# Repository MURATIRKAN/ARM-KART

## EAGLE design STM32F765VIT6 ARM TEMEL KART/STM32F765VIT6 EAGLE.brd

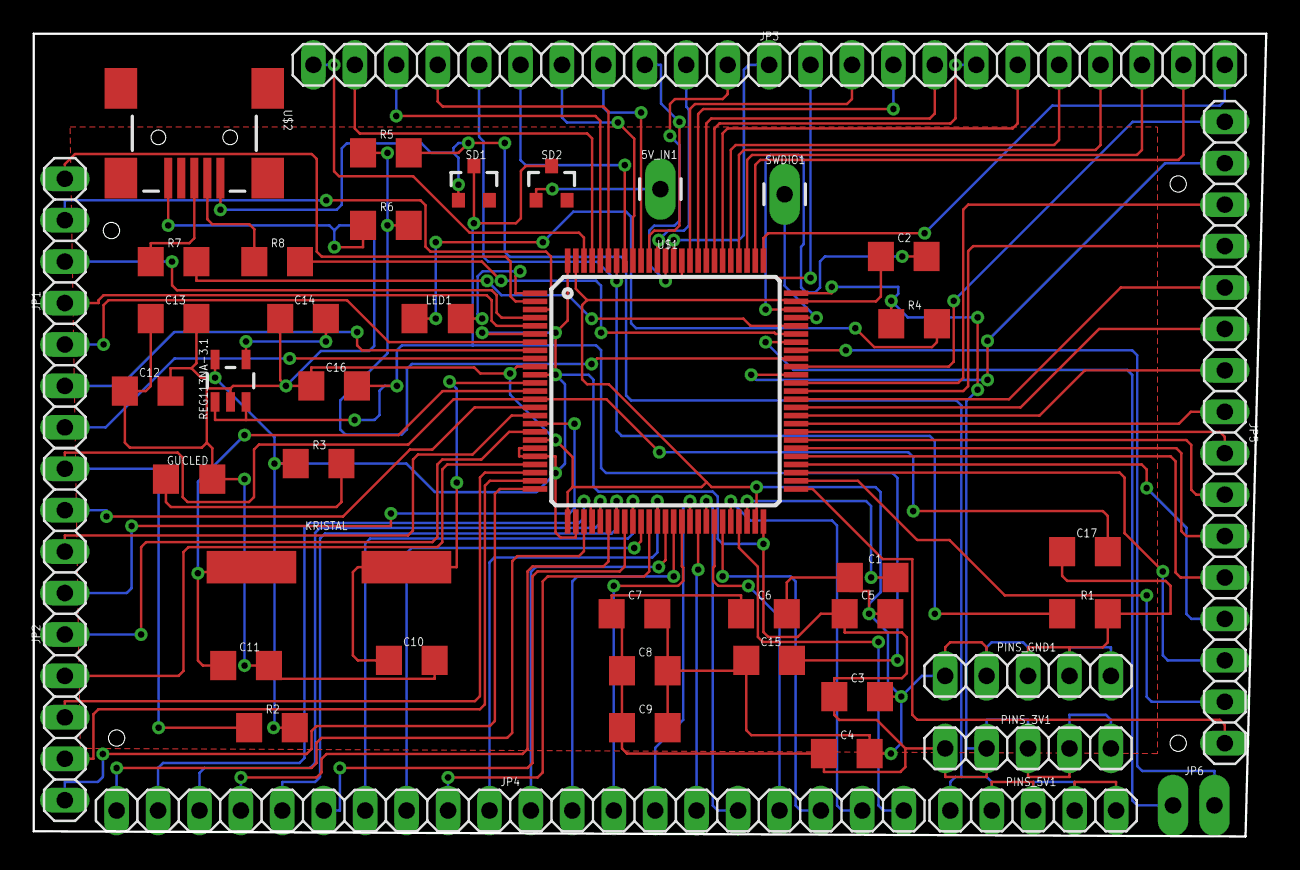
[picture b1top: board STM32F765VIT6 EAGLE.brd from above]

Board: 2 copper layers, 75.6 x 49.2 mm, 44 parts (0 on the bottom side), 95 nets.

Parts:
5V_IN1: M01PTH_LONGPAD (M01); 1X01_LONGPAD
C1, C2, C9: 2uF2; 1206
C3, C4, C5, C6, C7, C17: 100nF; 1206
C8, C12, C13, C14, C15, C16: 10nF; 1206
C10, C11: 18pF; 1206
GUCLED: GREEN; 1206_GUCLED
JP1: PINHD-1X07_2.54 (PINHD-1X07); 1X07
JP2: PINHD-1X09_2.54 (PINHD-1X09); 1X09
JP3: PINHD-1X23_2.54 (PINHD-1X23); 1X23
JP4: PINHD-1X20_2.54 (PINHD-1X20); 1X20
JP5: PINHD-1X16_2.54 (PINHD-1X16); 1X16
JP6: M02; 1X02_LONGPADS
KRISTAL: 8MHZ; CSM-7X-DU
LED1: BLUE; 1206_GUCLED
PINS_3V1, PINS_5V1: PINHD-1X05_2.54 (PINHD-1X05); 1X05
PINS_GND1: PINHD-1X05_2.54 (PINHD-1X05); 1X05
R1, R2: 10K; 1206
R3, R4: 330; 1206
R5: 15K; 1206
R6: 22K; 1206
R7, R8: 22; 1206
REG113NA-3.1: V_REG_LDOSMD (V_REG_LDO); SOT23-5
SD1, SD2: 400mA/40V/470mV; SOT23-3
SWDIO1: M01PTH_LONGPAD (M01); 1X01_LONGPAD
U$1: STM32F765VIT6; LQFP100
U$2: USB-MINIB-5PIN (USB-MINIB); USB-MINIB

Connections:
2_PE3: JP1.7, U$1.2
3V3: C3.1, C4.1, C5.1, C6.1, C7.1, C8.1, C9.1, C12.2, C13.2, PINS_3V1.1, PINS_3V1.2, PINS_3V1.3, PINS_3V1.4, PINS_3V1.5, R2.2, R3.1, R4.1, REG113NA-3.1.5, U$1.6, U$1.11, U$1.20, U$1.21, U$1.27, U$1.50, U$1.75, U$1.100
3_PE4: JP1.6, U$1.3
4_PE5: JP1.5, U$1.4
5V: 5V_IN1.1, SD2.1
5_PE6: JP1.4, U$1.5
7_PC13: JP1.3, U$1.7
8_PC14: JP1.2, U$1.8
9_PC15: JP1.1, U$1.9
15_PC0: JP2.8, U$1.15
16_PC1: JP2.7, U$1.16
17_PC2: JP2.6, U$1.17
18_PC3: JP2.5, U$1.18
22_PA0: JP2.4, U$1.22
23_PA1: JP2.3, U$1.23
24_PA2: JP2.2, U$1.24
25_PA3: JP2.1, U$1.25
28_PA4: JP4.1, U$1.28
29_PA5: JP4.2, U$1.29
30_PA6: JP4.3, U$1.30
31_PA7: JP4.4, U$1.31
32_PC4: JP4.5, U$1.32
33_PC5: JP4.6, U$1.33
34_PB0: JP4.7, U$1.34
35_PB1: JP4.8, U$1.35
36_PB2: JP4.9, U$1.36
37_PE7: JP4.10, U$1.37
38_PE8: JP4.11, U$1.38
39_PE9: JP4.12, U$1.39
40_PE10: JP4.13, U$1.40
41_PE11: JP4.14, U$1.41
42_PE12: JP4.15, U$1.42
43_PE13: JP4.16, U$1.43
44_PE14: JP4.17, U$1.44
45_PE15: JP4.18, U$1.45
51_PB12: JP5.16, U$1.51
52_PB13: JP5.15, U$1.52
53_PB14: JP5.14, U$1.53
54_PB15: JP5.13, U$1.54
55_PD8: JP5.12, U$1.55
56_PD9: JP5.11, U$1.56
57_PD10: JP5.10, U$1.57
58_PD11: JP5.9, U$1.58
61_PD14: JP5.6, U$1.61
62_PD15: JP5.5, U$1.62
63_PC6: JP5.4, U$1.63
64_PC7: JP5.3, U$1.64
65_PC8: JP5.2, U$1.65
66_PC9: JP5.1, U$1.66
68_PA9: JP6.2, U$1.68
69_PA10: JP6.1, U$1.69
77_PA15: JP3.22, U$1.77
78_PC10: JP3.21, U$1.78
79_PC11: JP3.20, U$1.79
80_PC12: JP3.19, U$1.80
81_PD0: JP3.18, U$1.81
82_PD1: JP3.17, U$1.82
83_PD2: JP3.16, U$1.83
84_PD3: JP3.15, U$1.84
85_PD4: JP3.14, U$1.85
86_PD5: JP3.13, U$1.86
87_PD6: JP3.12, U$1.87
88_PD7: JP3.11, U$1.88
89_PB3: JP3.10, U$1.89
90_PB4: JP3.9, U$1.90
91_PB5: JP3.8, U$1.91
92_PB6: JP3.7, U$1.92
93_PB7: JP3.6, U$1.93
97_PE0: JP3.2, U$1.97
98_PE1: JP3.1, U$1.98
BOOT0: JP3.5, R1.1, U$1.94
GND: C1.1, C2.1, C3.2, C4.2, C5.2, C6.2, C7.2, C8.2, C9.2, C10.2, C11.2, C12.1, C13.1, C14.1, C15.1, C16.1, C17.1, GUCLED.2, PINS_GND1.1, PINS_GND1.2, PINS_GND1.3, PINS_GND1.4, PINS_GND1.5, R1.2, R6.1, REG113NA-3.1.2, U$1.10, U$1.19, U$1.26, U$1.49, U$1.74, U$1.99, U$2.GND
I2C1_SCL: JP3.4, U$1.95
I2C1_SDA: JP3.3, U$1.96
I2C2_SCL: JP4.19, U$1.46
I2C2_SDA: JP4.20, U$1.47
I2C4_SCL: JP5.8, U$1.59
I2C4_SDA: JP5.7, U$1.60
LED1: LED1.2, U$1.1
unnamed: LED1.1, R4.2
unnamed: C15.2, C16.2, REG113NA-3.1.1, REG113NA-3.1.3, SD1.3, SD2.3
unnamed: R8.1, U$2.D-
unnamed: R7.1, U$2.D+
NR: C14.2, REG113NA-3.1.4
OSC_IN: C10.1, KRISTAL.2, U$1.12
OSC_OUT: C11.1, KRISTAL.1, U$1.13
PA8: R5.1, R6.2, U$1.67
RESET: C17.2, JP2.9, R2.1, U$1.14
SWDCLK: JP3.23, U$1.76
SWDIO: SWDIO1.1, U$1.72
USBDM: R8.2, U$1.70
USBDP: R7.2, U$1.71
VCAP1: C1.2, U$1.48
VCAP2: C2.2, U$1.73
VUSB: PINS_5V1.1, PINS_5V1.2, PINS_5V1.3, PINS_5V1.4, PINS_5V1.5, R5.2, SD1.1, U$2.VBUS

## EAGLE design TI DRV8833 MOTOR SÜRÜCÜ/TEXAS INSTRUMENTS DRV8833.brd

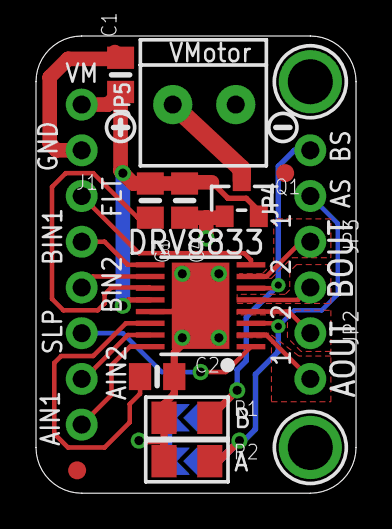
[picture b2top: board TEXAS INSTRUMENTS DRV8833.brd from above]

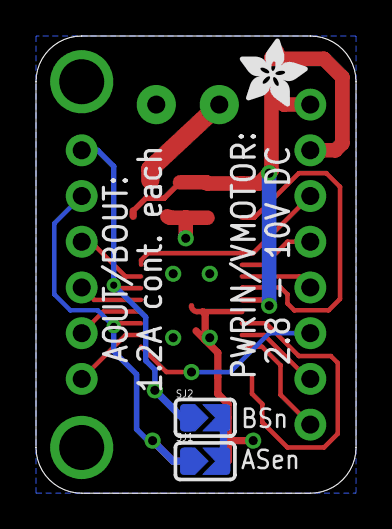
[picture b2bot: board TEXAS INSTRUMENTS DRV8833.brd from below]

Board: 2 copper layers, 17.8 x 25.4 mm, 22 parts (3 on the bottom side), 17 nets.

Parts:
C1, C4: 10µF/16V; 0805-NO
C2: 10µF; 0805-NO
C3: 0.1uF; 0805-NO
FID1, FID2: FIDUCIAL""; FIDUCIAL_1MM
J1: VMOTORIN; TERMBLOCK_1X2-3.5MM
JP2, JP3, JP4: 1X02_ROUND
JP5: 1X08_ROUND_70
Q1: DMG3415U; SOT23-WIDE
R1, R2: 0.2Ω; _1206
SJ1: ISENSEA; SOLDERJUMPER_ARROW_NOPASTE
SJ2: ISENSEB; SOLDERJUMPER_ARROW_NOPASTE
U1: DRV8833PWPR; HTSSOP16
U$13, U$14: MOUNTINGHOLE2.5; MOUNTINGHOLE_2.5_PLATED
U$15: SYMBOL_PLUS
U$16: SYMBOL_MINUS
U$17: ADAFRUIT_3.5MM

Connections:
!SLEEP: JP5.6, U1.1
AIN1: JP5.8, U1.16
AIN2: JP5.7, U1.15
AOUT1: JP2.2, U1.2
AOUT2: JP2.1, U1.4
ASEN: JP4.1, R2.2, SJ1.1, U1.3
BIN1: JP5.4, U1.9
BIN2: JP5.5, U1.10
BOUT1: JP3.1, U1.7
BOUT2: JP3.2, U1.5
BSEN: JP4.2, R1.2, SJ2.1, U1.6
GND: C1.2, C2.2, C4.2, J1.2, JP5.2, Q1.1, R1.1, R2.1, SJ1.2, SJ2.2, U1.13, U1.PPAD
unnamed: C3.2, U1.11
NFAULT: JP5.3, U1.8
PWRIN: J1.1, Q1.3
VINT: C2.1, U1.14
VMOTOR: C1.1, C3.1, C4.1, JP5.1, Q1.2, U1.12

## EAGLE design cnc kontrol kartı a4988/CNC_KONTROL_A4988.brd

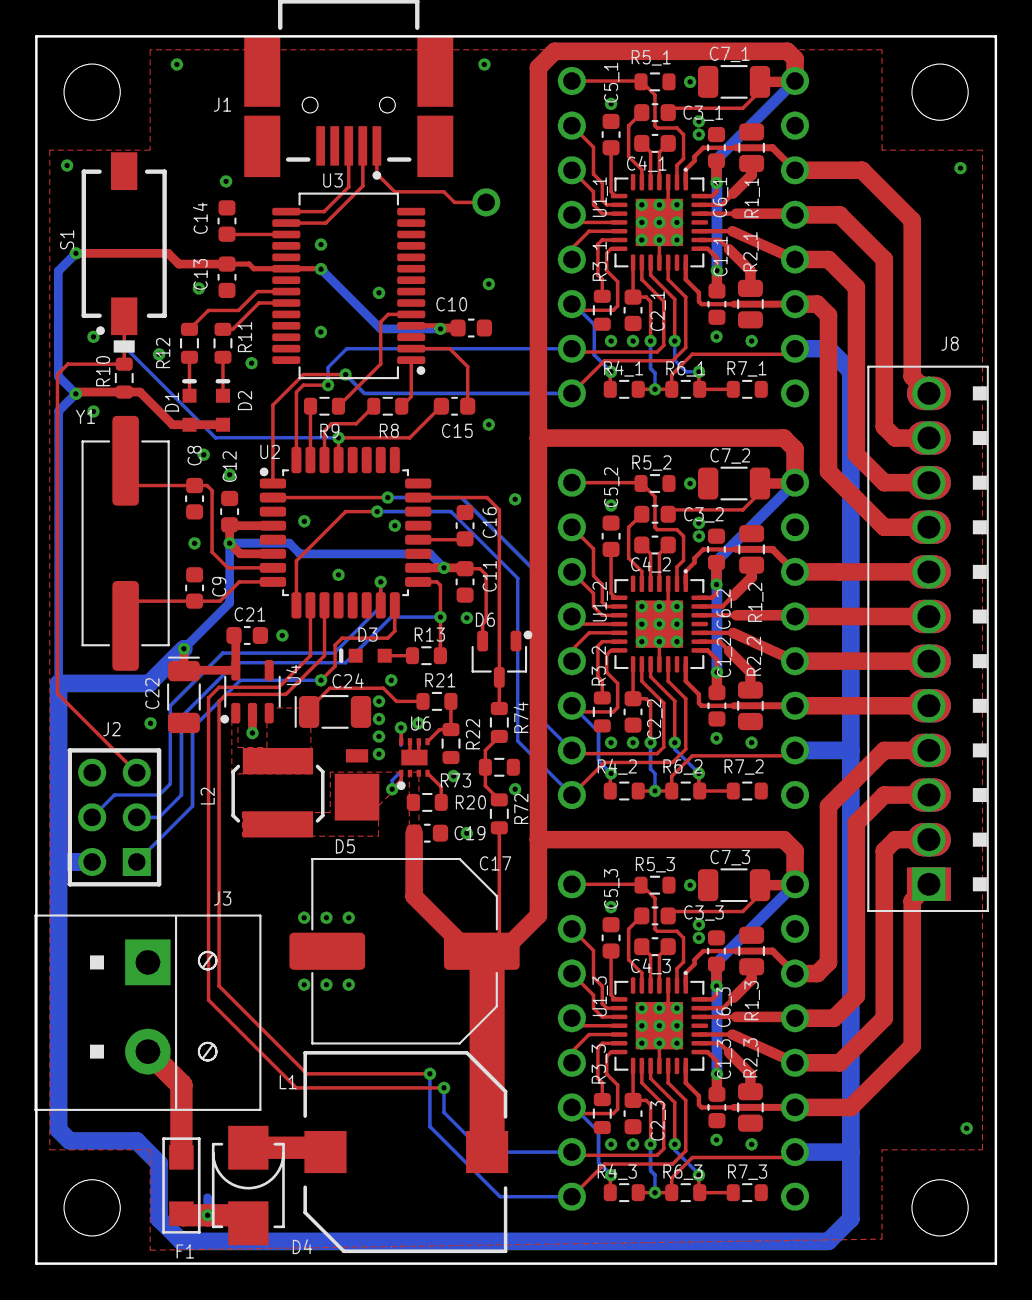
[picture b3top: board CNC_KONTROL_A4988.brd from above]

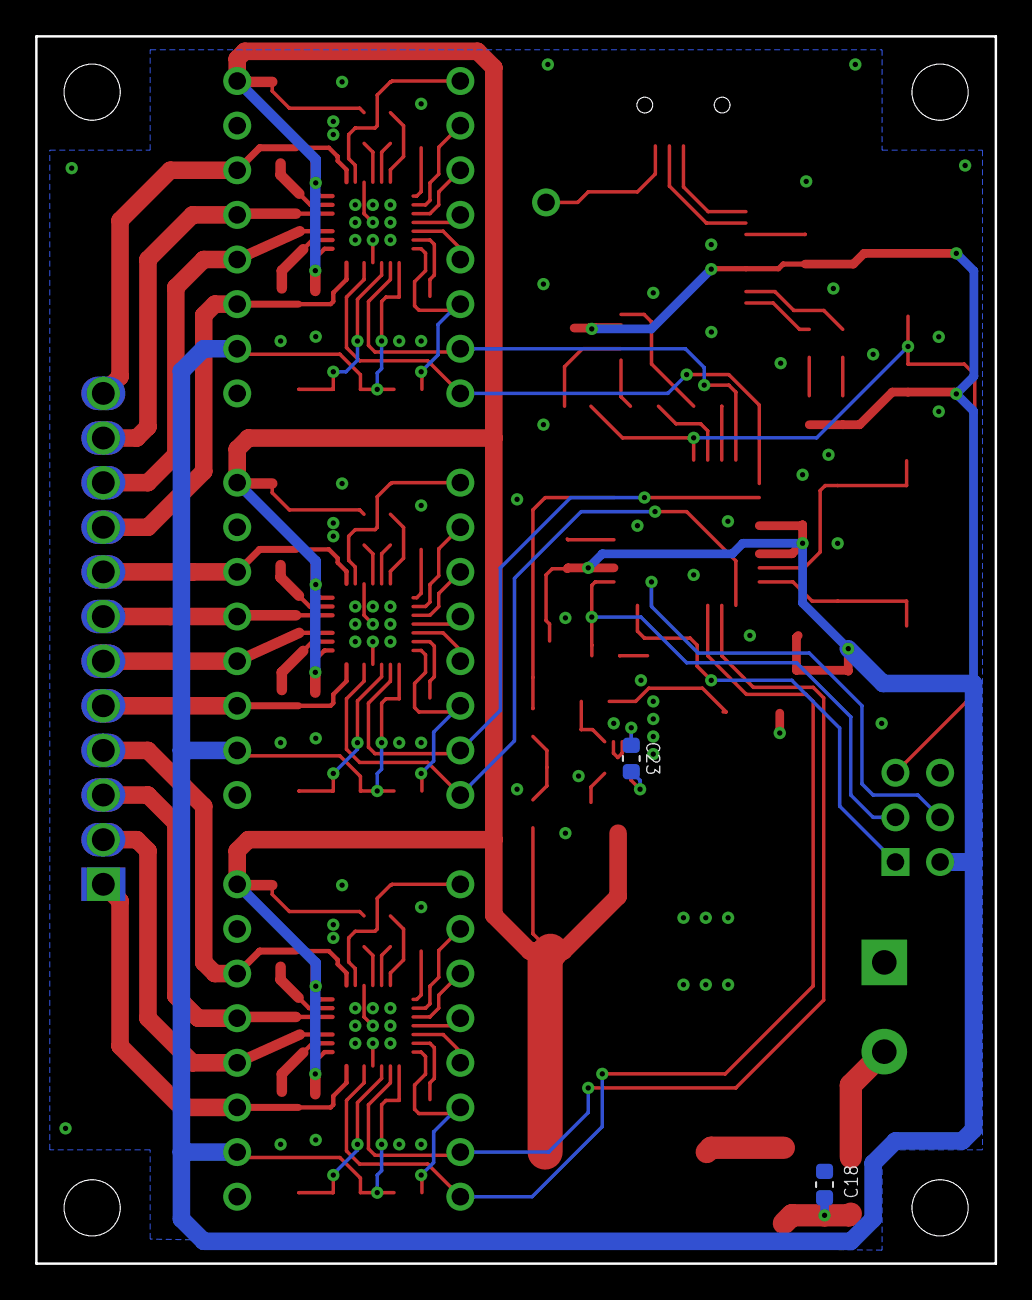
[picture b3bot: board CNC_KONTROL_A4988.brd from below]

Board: 2 copper layers, 54.6 x 69.8 mm, 141 parts (2 on the bottom side), 94 nets.

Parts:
C1_1: 100n; CAP_1608_N
C1_2, C1_3: 100n; CAP_1608_N_C1_2
C2_1, C2_2, C2_3: 0.22u; CAP_1608_N_C11
C3_1, C3_2, C3_3, C6_1: 100n; CAP_1608_N_C3_1
C4_1: 100n; CAP_1608_N_C4_1
C4_2, C4_3, C11, C14, C15: 100n; CAP_1608_N_C11
C5_1, C5_2, C5_3: 0.22u; CAP_1608_N_C5_1
C6_2, C6_3: 100n; CAP_1608_N_C6_2
C7_1, C7_2, C7_3: 4.7u; CAP_3216_N
C8: 16p; CAP_1608_N
C9: 16p; CAP_1608_N_C9
C10: 100n; CAP_1608_N_C10
C12: 100n; CAP_1608_N_C12
C13, C16: 100n; CAP_1608_N_C9
C17: 220 uF 35V; CAPAE1030X1050L350X90N
C18: 0.1uF; CAP_1608_N_C18
C19: 0.1uF; CAP_1608_N_C19
C21: 0.1uF; CAP_1608_N_C21
C22: 22uF; CAPP_3216_N
C23: 10nF; CAP_1608_N_C18
C24: 22uF; CAPP_3216_N_C24
D1: APG1608CGKC/T; KINGBRIGHT_APG1608CGKC_T
D2, D3: APG1608CGKC/T; KINGBRIGHT_APG1608CGKC_T_D2
D4: S3AB-13_SMB; SMB-DIODE-2K
D5: MBRM130LT1G
D6: BAT54ALT1G; SOT23-3P95_240X110L43X44N
DIR_1: DIR; TP
DIR_2: DIR; TP_DIR_2
DIR_3: DIR; TP_DIR_3
EN_1, EN_2: EN; TP
EN_3: EN; TP_EN_3
F1: C1S5; 1206NW
GND_1, GND_2, GND_3: GND; TP_GND_1
J1: 0678038020; MOLEX_0678038020
J2: ICSP
J3: 1546074-2; TE_TB-1X2_5.08_11X13_SC_A35
J8: OSTVN12A150; OST_TB-1X12_2.54_31X7_SC_H
L1: 22uH; SDR1105-220ML
L2: 8.2uH; SRN50408R2M
MS1_1, MS1_2: MS1; TP
MS1_3: MS1; TP_MS1_3
MS2_1, MS2_2: MS2; TP
MS2_3: MS2; TP_MS2_3
MS3_1, MS3_2, MS3_3: MS3; TP
OUT1A_1, OUT1A_2, OUT1A_3: 1A; TP_GND_1
OUT1B_1, OUT1B_2, OUT1B_3: 1B; TP_GND_1
OUT2A_1, OUT2A_2, OUT2A_3: 2A; TP_GND_1
OUT2B_1, OUT2B_2, OUT2B_3: 2B; TP_GND_1
R1_1, R1_2, R1_3, R2_1, R2_2, R2_3: 0.05; RES_2012_N
R3_1, R3_2, R3_3: 10K; RES_1608_N_R3_1
R4_1, R4_2, R4_3: 100K; RES_1608_N
R5_1: 100K; RES_1608_N_R5_1
R5_2, R5_3: 100K; RES_1608_N_R10
R6_1, R6_2, R6_3: 20K; RES_1608_N
R7_1, R7_2, R7_3: *; RES_1608_N_R10
R8, R9, R13: 1K; RES_1608_N
R10: 10K; RES_1608_N_R10
R11: 1K; RES_1608_N_R10
R12: 1K; RES_1608_N_R12
R20: 10k; RES_1608_N_R20
R21: 73.2k 1%; RES_1608_N_R21
R22: 7.15k 1%; RES_1608_N_R22
R72: 330k 1%; RES_1608_N_R72
R73: 20.0k 1%; RES_1608_N_R73
R74: 100; RES_1608_N_R21
RST_1, RST_3: RST; TP
RST_2: RST; TP_RST_2
S1: BPA01SB; CK_BPA-01S
SLEEP_1: SLEEP; TP_SLEEP_1
SLEEP_2: SLEEP; TP_SLEEP_2
SLEEP_3: SLEEP; TP_SLEEP_3
STEP_1: STEP; TP
STEP_2: STEP; TP_STEP_2
STEP_3: STEP; TP_STEP_3
TP_1, TP_2, TP_3: GND; TP_GND_1
U1_1, U1_2: A4988; QFN29P50_500X500X90L60X23T270N
U1_3: A4988; QFN29P50_500X500X90L60X23T270N_U1_3
U2: ATMEGA328P-AU; QFP32P80_900X900X120L60X37N_AD2
U3: FT232RL-TUBE; SOP28P65_1020X780X200L75X30N_AD2
U4: TPS76350DBV; SOT23-5P95_275X110L40X32N
U6: AOZ1281
VDD_1, VDD_2, VDD_3: VDD; TP_GND_1
VMT_1, VMT_2, VMT_3: VMT; TP_GND_1
VUSB: TP; TP_VUSB
Y1: HC49/4HSMX; XTAL1140X490X430D1340L450X60N

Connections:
9V: C24.1, L2.2, R21.1, U4.1, U4.3
GND: C1_1.2, C1_2.2, C1_3.2, C2_1.2, C2_2.2, C2_3.2, C5_1.2, C5_2.2, C5_3.2, C6_1.2, C6_2.2, C6_3.2, C7_1.2, C7_2.2, C7_3.2, C8.2, C9.2, C10.2, C11.2, C12.2, C13.2, C14.2, C16.2, C17.2, C18.2, C19.2, C21.2, C22.2, C24.2, D3.2, D5.2, D6.1, GND_1.1, GND_2.1, GND_3.1, J1.5, J1.6, J2.6, J3.1, R1_1.1, R1_2.1, R1_3.1, R2_1.1, R2_2.1, R2_3.1, R3_1.2, R3_2.2, R3_3.2, R5_1.1, R5_2.1, R5_3.1, R7_1.1, R7_2.1, R7_3.1, R22.2, R73.2, S1.2, TP_1.1, TP_2.1, TP_3.1, U1_1.3, U1_1.18, U1_1.29, U1_2.3, U1_2.18, U1_2.29, U1_3.3, U1_3.18, U1_3.29, U2.3, U2.5, U2.21, U3.7, U3.18, U3.21, U3.25, U3.26, U4.2, U6.6, U6.7, U6.9
Net_0_1: R1_1.2, U1_1.27
Net_0_2: R1_2.2, U1_2.27
Net_0_3: R1_3.2, U1_3.27
Net_1: D3.1, R13.1
Net_2_1: R2_1.2, U1_1.23
Net_2_2: R2_2.2, U1_2.23
Net_2_3: R2_3.2, U1_3.23
Net_7: D6.3, R74.1, U2.23
Net_8: C2_1.1, C2_2.1, C2_3.1, C10.1, C11.1, C12.1, C13.1, C21.1, C22.1, D1.1, D2.1, D6.2, J2.2, R4_1.2, R4_2.2, R4_3.2, R6_1.1, R6_2.1, R6_3.1, R10.2, U1_1.15, U1_2.15, U1_3.15, U2.4, U2.6, U2.18, U3.4, U3.20, U4.5, VDD_1.1, VDD_2.1, VDD_3.1
Net_11_1: C3_1.2, U1_1.6
Net_11_2: C3_2.2, U1_2.6
Net_11_3: C3_3.2, U1_3.6
Net_12_1: C4_1.1, U1_1.4
Net_12_2: C4_2.1, U1_2.4
Net_12_3: C4_3.1, U1_3.4
Net_13_1: C4_1.2, U1_1.5
Net_13_2: C4_2.2, U1_2.5
Net_13_3: C4_3.2, U1_3.5
Net_14_1: C5_1.1, U1_1.8
Net_14_2: C5_2.1, U1_2.8
Net_14_3: C5_3.1, U1_3.8
Net_15_1: R3_1.1, U1_1.13
Net_15_2: R3_2.1, U1_2.13
Net_15_3: R3_3.1, U1_3.13
Net_16_1: R4_1.1, SLEEP_1.1, U1_1.14
Net_16_2: R4_2.1, SLEEP_2.1, U1_2.14
Net_16_3: R4_3.1, SLEEP_3.1, U1_3.14
Net_17_1: MS1_1.1, U1_1.9
Net_17_2: MS1_2.1, U1_2.9
Net_17_3: MS1_3.1, U1_3.9
Net_18_1: MS2_1.1, U1_1.10
Net_18_2: MS2_2.1, U1_2.10
Net_18_3: MS2_3.1, U1_3.10
Net_19_1: MS3_1.1, U1_1.11
Net_19_2: MS3_2.1, U1_2.11
Net_19_3: MS3_3.1, U1_3.11
Net_20_1: EN_1.1, R5_1.2, U1_1.2
Net_20_2: EN_2.1, R5_2.2, U1_2.2
Net_20_3: EN_3.1, R5_3.2, U1_3.2
Net_21_1: RST_1.1, U1_1.12
Net_21_2: RST_2.1, U1_2.12
Net_21_3: RST_3.1, U1_3.12
Net_22_1: R6_1.2, R7_1.2, U1_1.17
Net_22_2: R6_2.2, R7_2.2, U1_2.17
Net_22_3: R6_3.2, R7_3.2, U1_3.17
Net_23: J1.3, U3.15
Net_24: J1.2, U3.16
Net_25: R8.1, U3.1
Net_26: R9.1, U3.5
Net_27: R8.2, U2.30
Net_28: R9.2, U2.31
Net_29: C9.1, U2.8, Y1.1
Net_30: C8.1, U2.7, Y1.2
Net_31: J2.4, U2.15
Net_32: J2.1, U2.16
Net_33: J2.3, R13.2, U2.17
Net_34: C15.2, J2.5, R10.1, S1.1, U2.29
Net_35: J1.1, VUSB.1
Net_36: C14.1, U3.17
Net_37: C15.1, U3.2
Net_38: C16.1, U2.20
Net_39: J8.10, OUT1A_1.1, U1_1.24
Net_40: J8.9, OUT1B_1.1, U1_1.21
Net_41: J8.11, OUT2A_1.1, U1_1.26
Net_42: J8.12, OUT2B_1.1, U1_1.1
Net_43: J8.6, OUT1A_2.1, U1_2.24
Net_44: J8.5, OUT1B_2.1, U1_2.21
Net_45: J8.7, OUT2A_2.1, U1_2.26
Net_46: J8.8, OUT2B_2.1, U1_2.1
Net_47: J8.2, OUT1A_3.1, U1_3.24
Net_48: J8.1, OUT1B_3.1, U1_3.21
Net_49: J8.3, OUT2A_3.1, U1_3.26
Net_50: J8.4, OUT2B_3.1, U1_3.1
Net_51: STEP_1.1, U1_1.16, U2.32
Net_52: DIR_1.1, U1_1.19, U2.1
Net_53: STEP_2.1, U1_2.16, U2.2
Net_54: DIR_2.1, U1_2.19, U2.9
Net_55: STEP_3.1, U1_3.16, U2.10
Net_56: DIR_3.1, U1_3.19, U2.11
Net_57: R11.2, U3.23
Net_58: R12.2, U3.22
Net_59: D1.2, R12.1
Net_60: D2.2, R11.1
Net_62: C18.1, D4.2, F1.2
Net_63: D4.1, L1.1
Net_94: F1.1, J3.2
Net_97: R72.2, R73.1, R74.2
Net_99: R20.2, U6.4
Net_100: C23.1, D5.1, L2.1, U6.1
Net_101: C23.2, U6.8
Net_103: R21.2, R22.1, U6.5
VMOT: C1_1.1, C1_2.1, C1_3.1, C3_1.1, C3_2.1, C3_3.1, C6_1.1, C6_2.1, C6_3.1, C7_1.1, C7_2.1, C7_3.1, C17.1, C19.1, L1.2, R20.1, R72.1, U1_1.22, U1_1.28, U1_2.22, U1_2.28, U1_3.22, U1_3.28, U6.2, U6.3, VMT_1.1, VMT_2.1, VMT_3.1
